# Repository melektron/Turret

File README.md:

# Turret
A turret, controlled by a raspberry pi and a pc

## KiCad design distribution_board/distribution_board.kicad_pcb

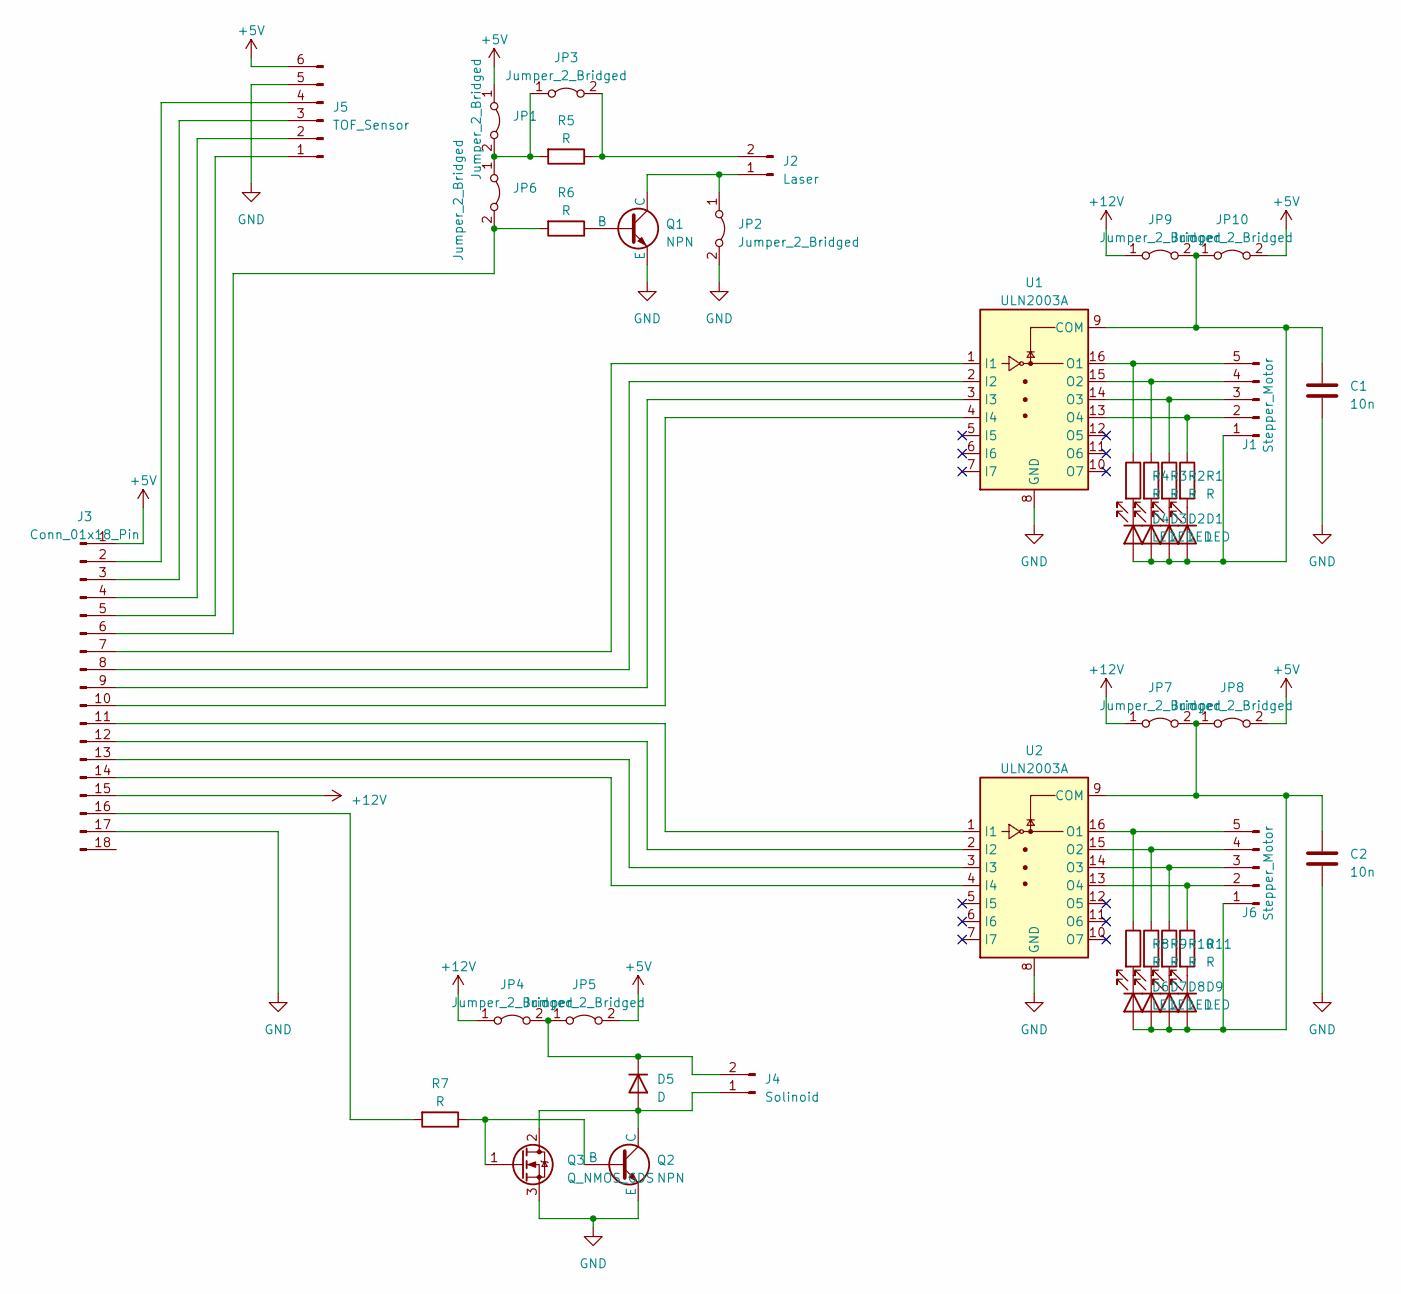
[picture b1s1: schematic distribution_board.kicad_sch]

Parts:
C1, C2: 10n; C_Disc_D5.0mm_W2.5mm_P5.00mm
D1, D2, D3, D4, D6, D7, D8, D9: LED; LED_D3.0mm
D5: D; D_A-405_P10.16mm_Horizontal
J1, J6: Stepper_Motor; JST_EH_B5B-EH-A_1x05_P2.50mm_Vertical
J2: Laser; JST_EH_B2B-EH-A_1x02_P2.50mm_Vertical
J3: Conn_01x18_Pin; PinSocket_1x18_P2.54mm_Vertical
J4: Solinoid; JST_EH_B2B-EH-A_1x02_P2.50mm_Vertical
J5: TOF_Sensor; JST_EH_B6B-EH-A_1x06_P2.50mm_Vertical
JP1, JP2, JP3, JP4, JP5, JP6, JP7, JP8, JP9, JP10: Jumper_2_Bridged; SolderJumper-2_P1.3mm_Bridged_RoundedPad1.0x1.5mm
Q1, Q2: NPN; TO-92_Wide
Q3: Q_NMOS_GDS; TO-220-3_Vertical
R1, R2, R3, R4, R5, R6, R7, R8, R9, R10, R11: R; R_Axial_DIN0207_L6.3mm_D2.5mm_P10.16mm_Horizontal
U1, U2: ULN2003A; DIP-16_W7.62mm_Socket

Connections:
+5V: J3.1, J5.6, JP1.1 (A), JP5.2 (B), JP8.2 (B), JP10.2 (B)
+12V: J3.15, JP4.1 (A), JP7.1 (A), JP9.1 (A)
GND: C1.2, C2.2, J3.17, J5.5, JP2.2 (B), Q1.3 (E), Q2.3 (E), Q3.3 (S), U1.8 (GND), U2.8 (GND)
unnamed: C1.1, D1.2 (A), D2.2 (A), D3.2 (A), D4.2 (A), J1.1, JP9.2 (B), JP10.1 (A), U1.9 (COM)
unnamed: D1.1 (K), R1.2
unnamed: D2.1 (K), R2.2
unnamed: D3.1 (K), R3.2
unnamed: D4.1 (K), R4.2
unnamed: D5.2 (A), J4.1, Q2.1 (C), Q3.2 (D)
unnamed: D5.1 (K), J4.2, JP4.2 (B), JP5.1 (A)
unnamed: C2.1, D6.2 (A), D7.2 (A), D8.2 (A), D9.2 (A), J6.1, JP7.2 (B), JP8.1 (A), U2.9 (COM)
unnamed: D6.1 (K), R8.2
unnamed: D7.1 (K), R9.2
unnamed: D8.1 (K), R10.2
unnamed: D9.1 (K), R11.2
unnamed: J1.2, R1.1, U1.13 (O4)
unnamed: J1.3, R2.1, U1.14 (O3)
unnamed: J1.4, R3.1, U1.15 (O2)
unnamed: J1.5, R4.1, U1.16 (O1)
unnamed: J2.1, JP2.1 (A), Q1.1 (C)
unnamed: J2.2, JP3.2 (B), R5.1
unnamed: J3.2, J5.4
unnamed: J3.3, J5.3
unnamed: J3.4, J5.2
unnamed: J3.5, J5.1
unnamed: J3.6, JP6.2 (B), R6.2
unnamed: J3.7, U1.1 (I1)
unnamed: J3.8, U1.2 (I2)
unnamed: J3.9, U1.3 (I3)
unnamed: J3.10, U1.4 (I4)
unnamed: J3.11, U2.1 (I1)
unnamed: J3.12, U2.2 (I2)
unnamed: J3.13, U2.3 (I3)
unnamed: J3.14, U2.4 (I4)
unnamed: J3.16, R7.2
unnamed: J6.2, R11.1, U2.13 (O4)
unnamed: J6.3, R10.1, U2.14 (O3)
unnamed: J6.4, R9.1, U2.15 (O2)
unnamed: J6.5, R8.1, U2.16 (O1)
unnamed: JP1.2 (B), JP3.1 (A), JP6.1 (A), R5.2
unnamed: Q1.2 (B), R6.1
unnamed: Q2.2 (B), Q3.1 (G), R7.1

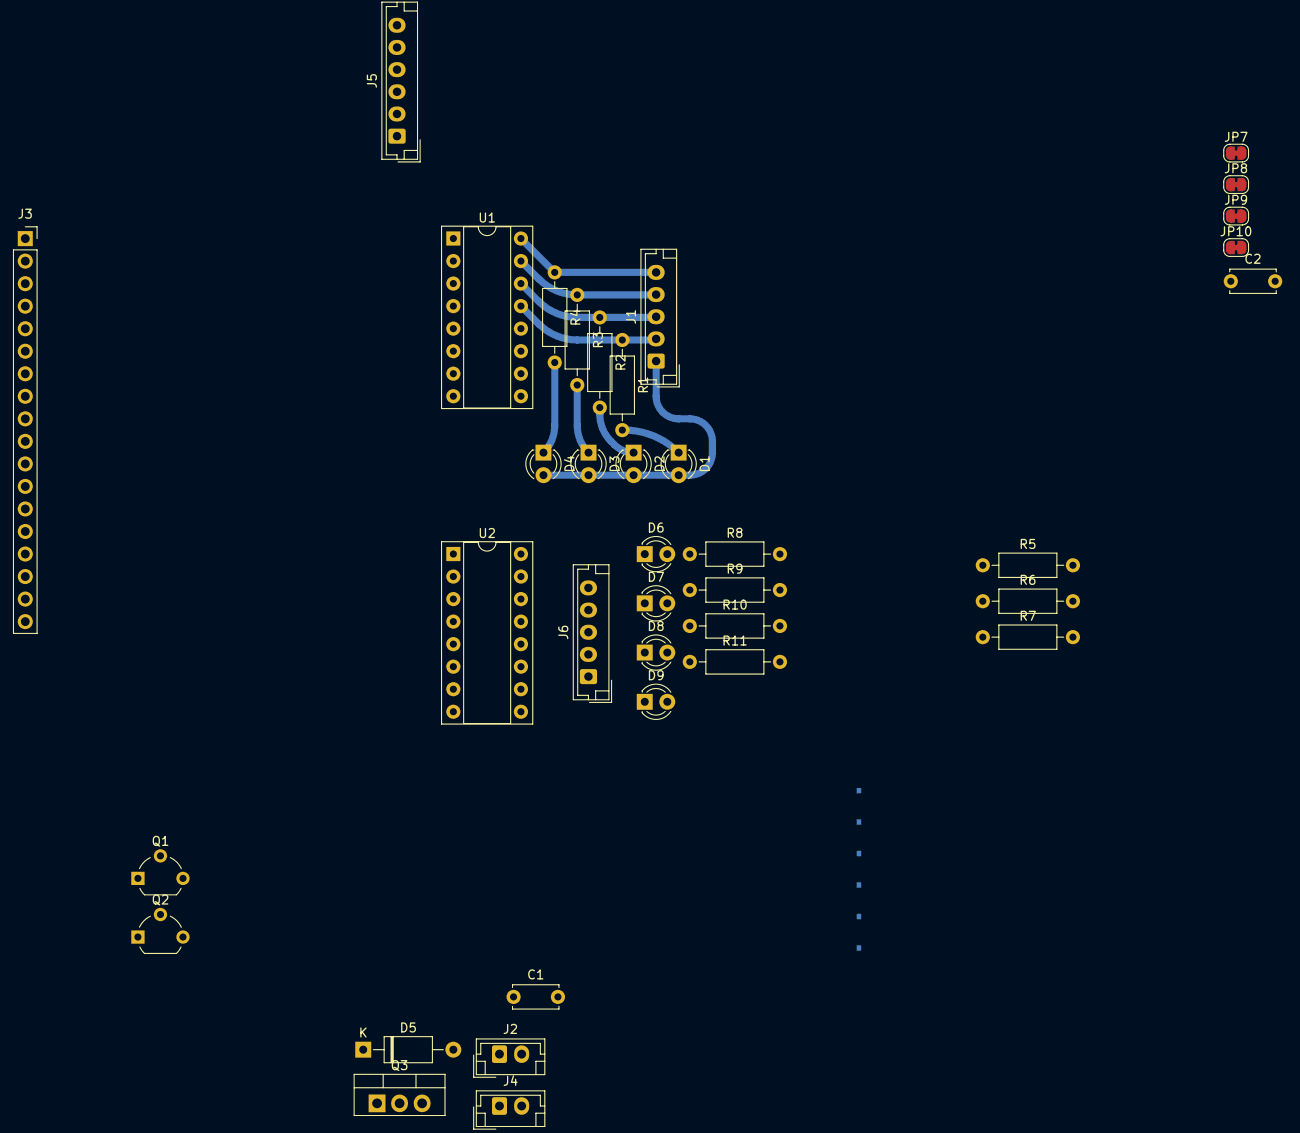
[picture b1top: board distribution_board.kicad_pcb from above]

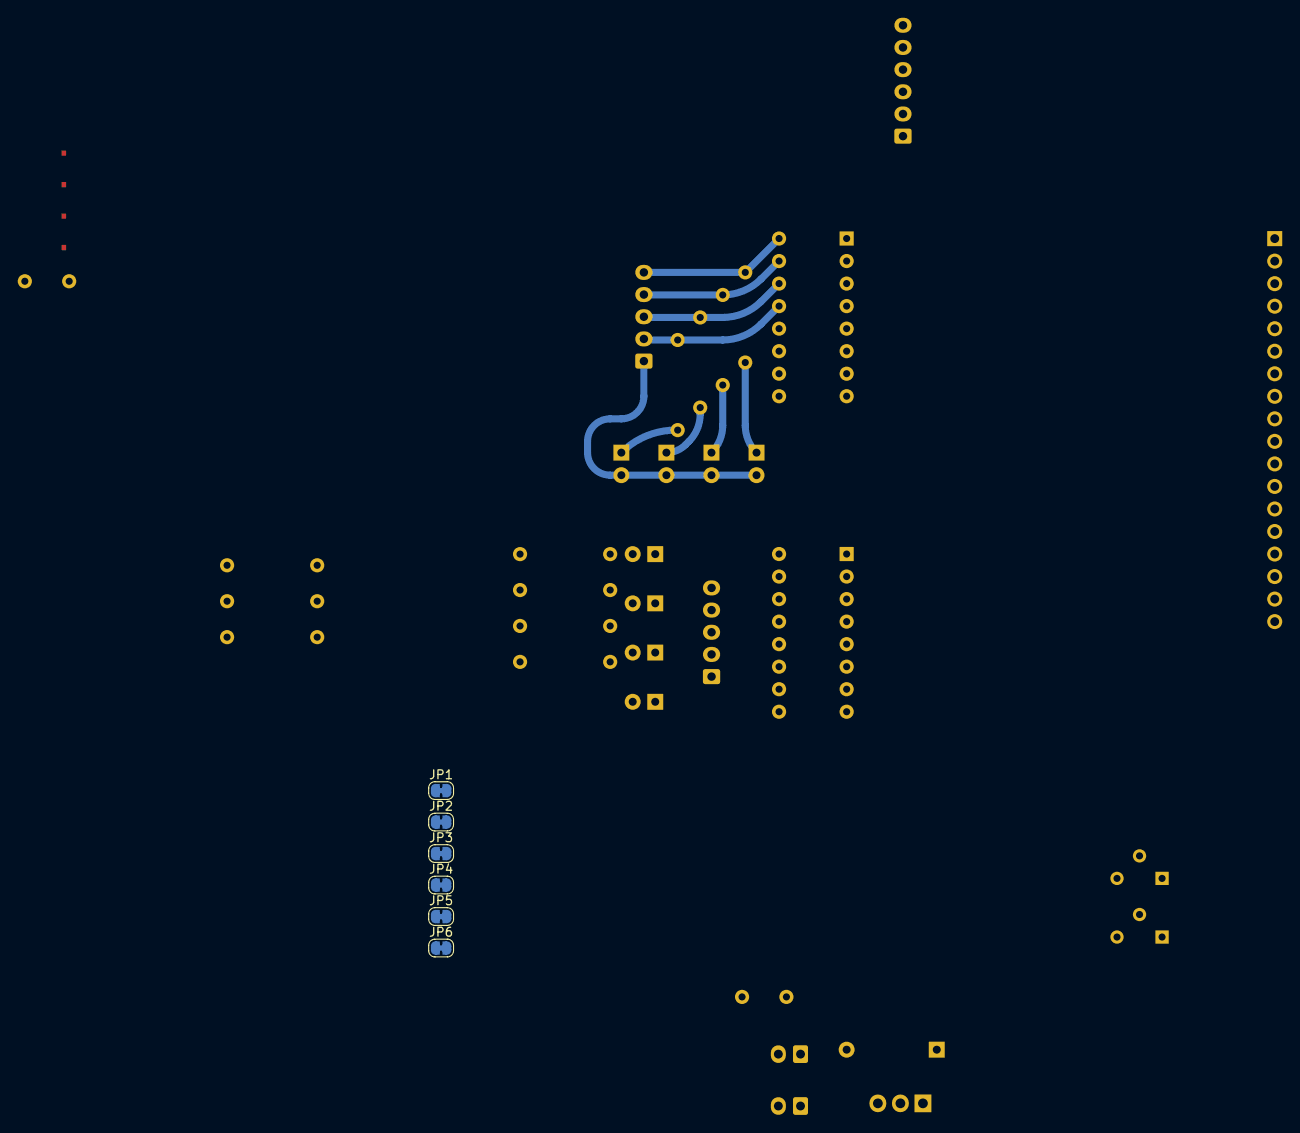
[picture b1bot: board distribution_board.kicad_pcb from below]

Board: 2 copper layers, 43 parts (6 on the bottom side), 42 nets.

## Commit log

2023-04-22 some testing
2023-04-24 created pcb
2023-04-24 board schematic and layout start
